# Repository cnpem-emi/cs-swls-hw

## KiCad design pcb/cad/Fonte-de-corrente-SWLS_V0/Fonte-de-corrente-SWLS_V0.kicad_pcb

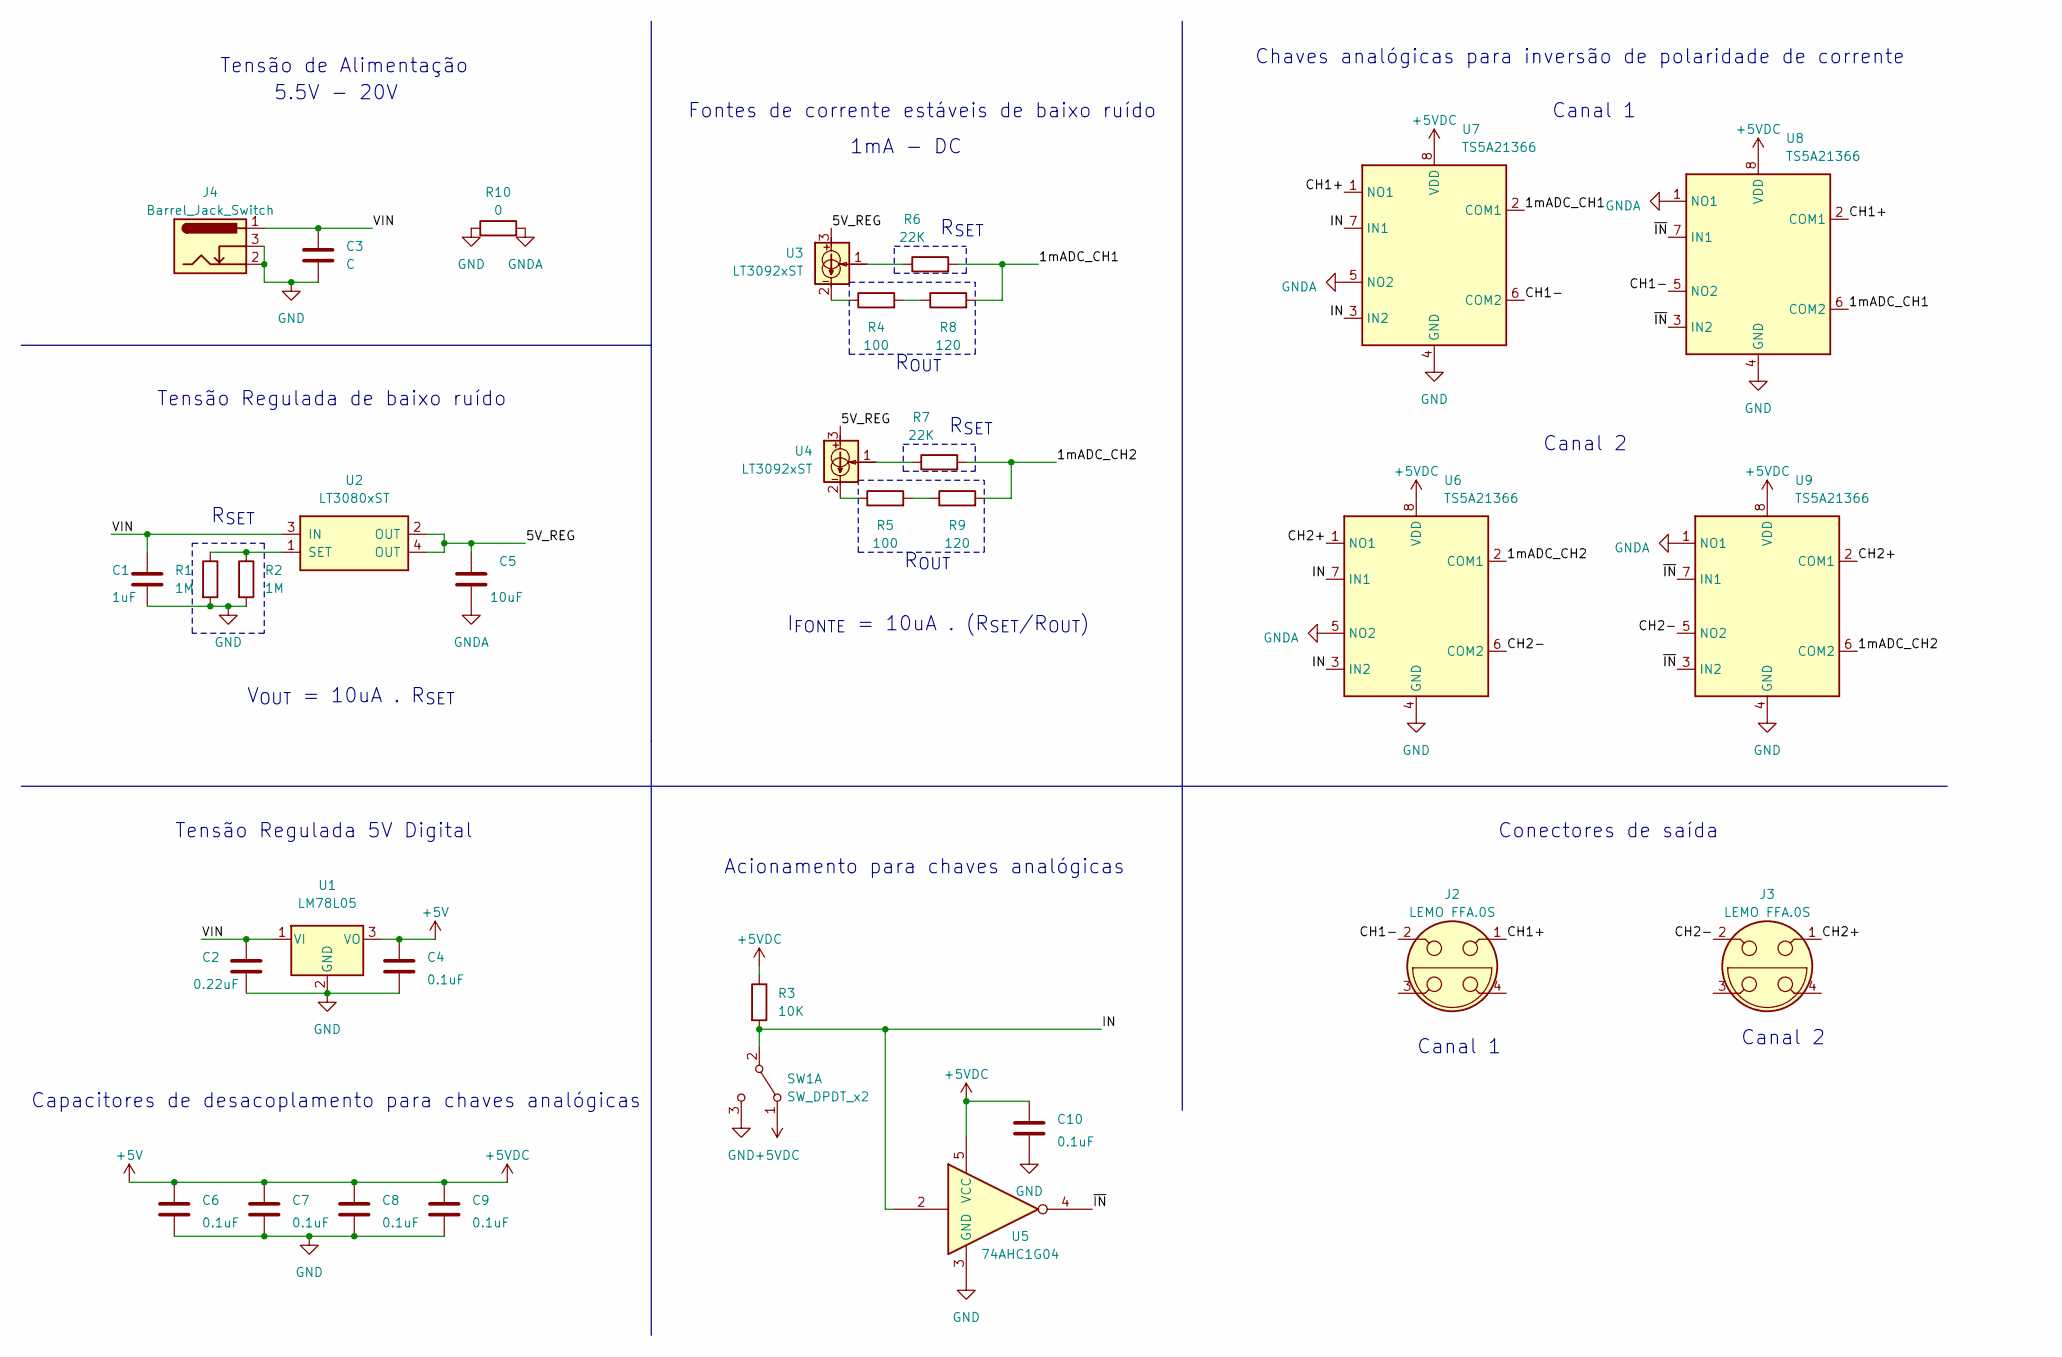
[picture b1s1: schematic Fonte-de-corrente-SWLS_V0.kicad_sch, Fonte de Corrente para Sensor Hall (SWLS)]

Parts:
C1: 1uF; C_0805_2012Metric
C2: 0.22uF; C_0805_2012Metric
C3: C; C_0805_2012Metric
C4, C10: 0.1uF; C_0805_2012Metric
C5: 10uF; C_0805_2012Metric
C6, C7, C8, C9: 0.1uF; C_1206_3216Metric
J2, J3: LEMO FFA.0S; EPG.0B.302.HLN
J4: Barrel_Jack_Switch; BarrelJack_GCT_DCJ200-10-A_Horizontal
R1, R2: 1M; R_0805_2012Metric
R3: 10K; R_0805_2012Metric
R4, R5: 100; R_0805_2012Metric
R6, R7: 22K; R_0805_2012Metric
R8, R9: 120; R_0805_2012Metric
R10: 0; R_0805_2012Metric
SW1: SW_DPDT_x2; SW_100SP1T2B4M6QE
U1: LM78L05; TO-92
U2: LT3080xST; SOT-223
U3, U4: LT3092xST; SOT-223-3_TabPin2
U5: 74AHC1G04; SOT-353_SC-70-5_Handsoldering
U6, U7, U8, U9: TS5A21366; VSSOP-8_2.4x2.1mm_P0.5mm

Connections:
+5V: C4.1, C6.1, C7.1, C8.1, C9.1, C10.1, R3.1, SW1.1 (A), U1.3 (VO), U5.5 (VCC), U6.8 (VDD), U7.8 (VDD), U8.8 (VDD), U9.8 (VDD)
/1mADC_CH1: R6.2, R8.2, U7.2 (COM1), U8.6 (COM2)
/1mADC_CH2: R7.2, R9.2, U6.2 (COM1), U9.6 (COM2)
/5V_REG: C5.1, U2.2 (OUT), U2.4 (OUT), U3.3, U4.3
/CH1+: J2.1, U7.1 (NO1), U8.2 (COM1)
/CH1-: J2.2, U7.6 (COM2), U8.5 (NO2)
/CH2+: J3.1, U6.1 (NO1), U9.2 (COM1)
/CH2-: J3.2, U6.6 (COM2), U9.5 (NO2)
/IN: R3.2, SW1.2 (B), U5.2, U6.3 (IN2), U6.7 (IN1), U7.3 (IN2), U7.7 (IN1)
/VIN: C1.1, C2.1, C3.1, J4.1, U1.1 (VI), U2.3 (IN)
/~IN: U5.4, U8.3 (IN2), U8.7 (IN1), U9.3 (IN2), U9.7 (IN1)
GND: C1.2, C2.2, C3.2, C4.2, C6.2, C7.2, C8.2, C9.2, C10.2, J2.5, J2.6, J2.7, J2.8, J3.5, J3.6, J3.7, J3.8, J4.2, J4.3, R1.2, R2.2, R10.1, SW1.3 (C), SW1.S1, SW1.S2, U1.2 (GND), U5.3 (GND), U6.4 (GND), U7.4 (GND), U8.4 (GND), U9.4 (GND)
GNDA: C5.2, R10.2, U6.5 (NO2), U7.5 (NO2), U8.1 (NO1), U9.1 (NO1)
unnamed: R4.1, U3.2
unnamed: R4.2, R8.1
unnamed: R5.1, U4.2
unnamed: R5.2, R9.1
unnamed: R6.1, U3.1
unnamed: R7.1, U4.1
unnamed: R1.1, R2.1, U2.1 (SET)

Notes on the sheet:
1mA - DC
Canal 2
Capacitores de desacoplamento para chaves analógicas
R_{OUT}
Canal 1
Chaves analógicas para inversão de polaridade de corrente
Tensão Regulada 5V Digital
Fontes de corrente estáveis de baixo ruído
Tensão de Alimentação
I_{FONTE} = 10uA . (R_{SET}/R_{OUT})
Conectores de saída
V_{OUT} = 10uA . R_{SET}
Tensão Regulada de baixo ruído
R_{SET}
5.5V - 20V
Acionamento para chaves analógicas

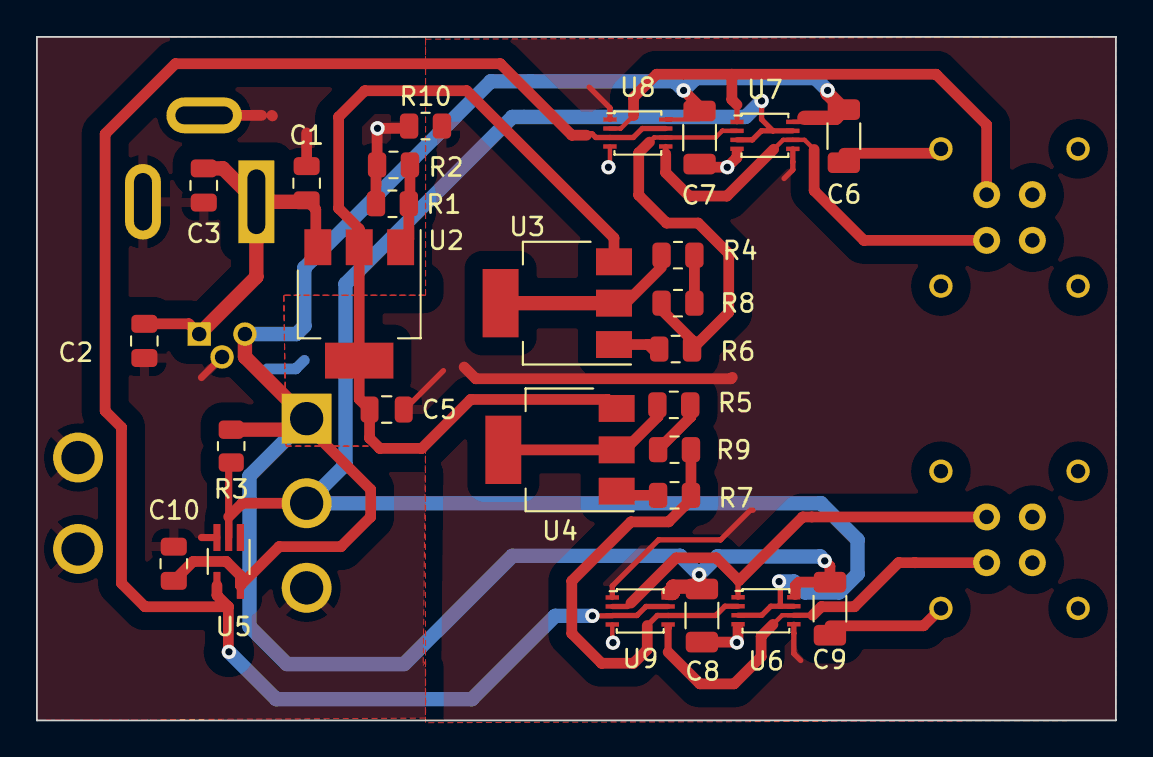
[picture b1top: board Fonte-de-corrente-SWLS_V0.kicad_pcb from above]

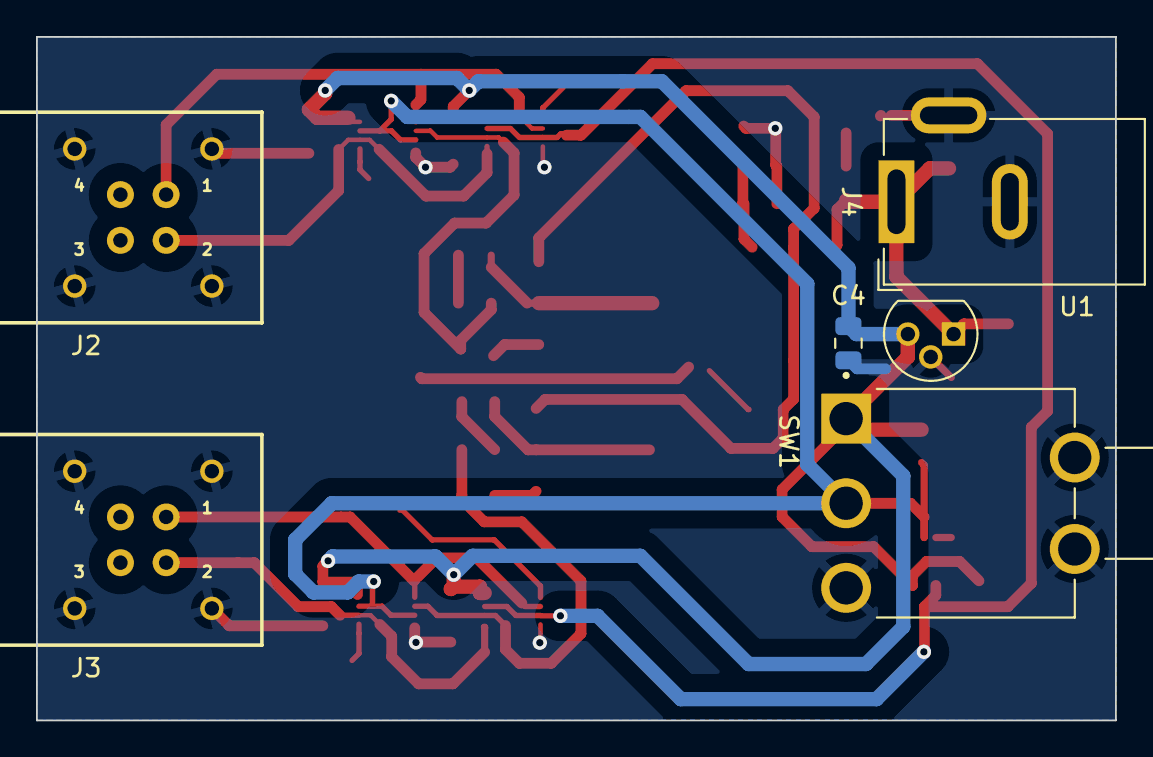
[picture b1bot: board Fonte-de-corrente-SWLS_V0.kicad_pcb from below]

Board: 2 copper layers, 59.9 x 38.0 mm, 33 parts (6 on the bottom side), 20 nets.

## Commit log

2023-05-11 Upload do esquemático da fonte de corrente
2023-05-11 Gerando PDF do esquemático
2023-05-11 Atualização do circuito esquemático, adição dos conectores lemo ff4.0s
2023-05-12 Atualização do circuito esquemático, adição de footprints nod componentes
2023-05-16 Incio do placement de fonte de corrente
2023-05-17 Atualização do pdf do esquemático
2023-05-17 Atualização do layout da PCB
2023-05-18 Atualização do layout de PCB
2023-05-23 Atualização do layout de PCB para revisão
2023-05-24 Atualização do layout de PCB com as correções indicadas nas issues
2023-05-24 Atualização do layout de PCB e esquemático com as correções indicadas nas issues
2023-05-24 Criação dos gerbers para a prototipagem da placa
2023-05-29 Atualização da ultima versão da PCB e esquemático
2023-07-17 Versão fabricada
